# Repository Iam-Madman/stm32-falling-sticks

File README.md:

# stm32-falling-sticks

A DIY reaction-based "falling sticks" game controller built around an STM32 Bluepill.

## Features

- **STM32 Bluepill** as the main controller
- **10x electromagnet drivers (12v)** — MOSFET-switched, each with a flyback protection diode and pulldown resistor
- **10x Hall effect sensors (5v)** for stick drop/position detection
- **LCD output** support for game status/score
- **Buzzer (12v)** support, driven off the same MOSFET channels as the electromagnets
- **Start button** input to trigger the game
- **Single-layer PCB** — 0-ohm jumper resistors used in place of vias/second layer for a few connections
- **CNC-mill optimized** trace layout (tested on a Wegstr 3-axis CNC)

## Power

- Dual 12V input options: screw terminal or DC jack
- **MP1584EN buck converter** steps 12V down to 5V to power the electromagnets, Hall effect sensors, and Bluepill

## Board Previews

| View | Image |
| --- | --- |
| **Top View** |  |
| **Bottom View** |  |
| **Side View 1** |  |
| **Side View 2** |  |

## Schematics

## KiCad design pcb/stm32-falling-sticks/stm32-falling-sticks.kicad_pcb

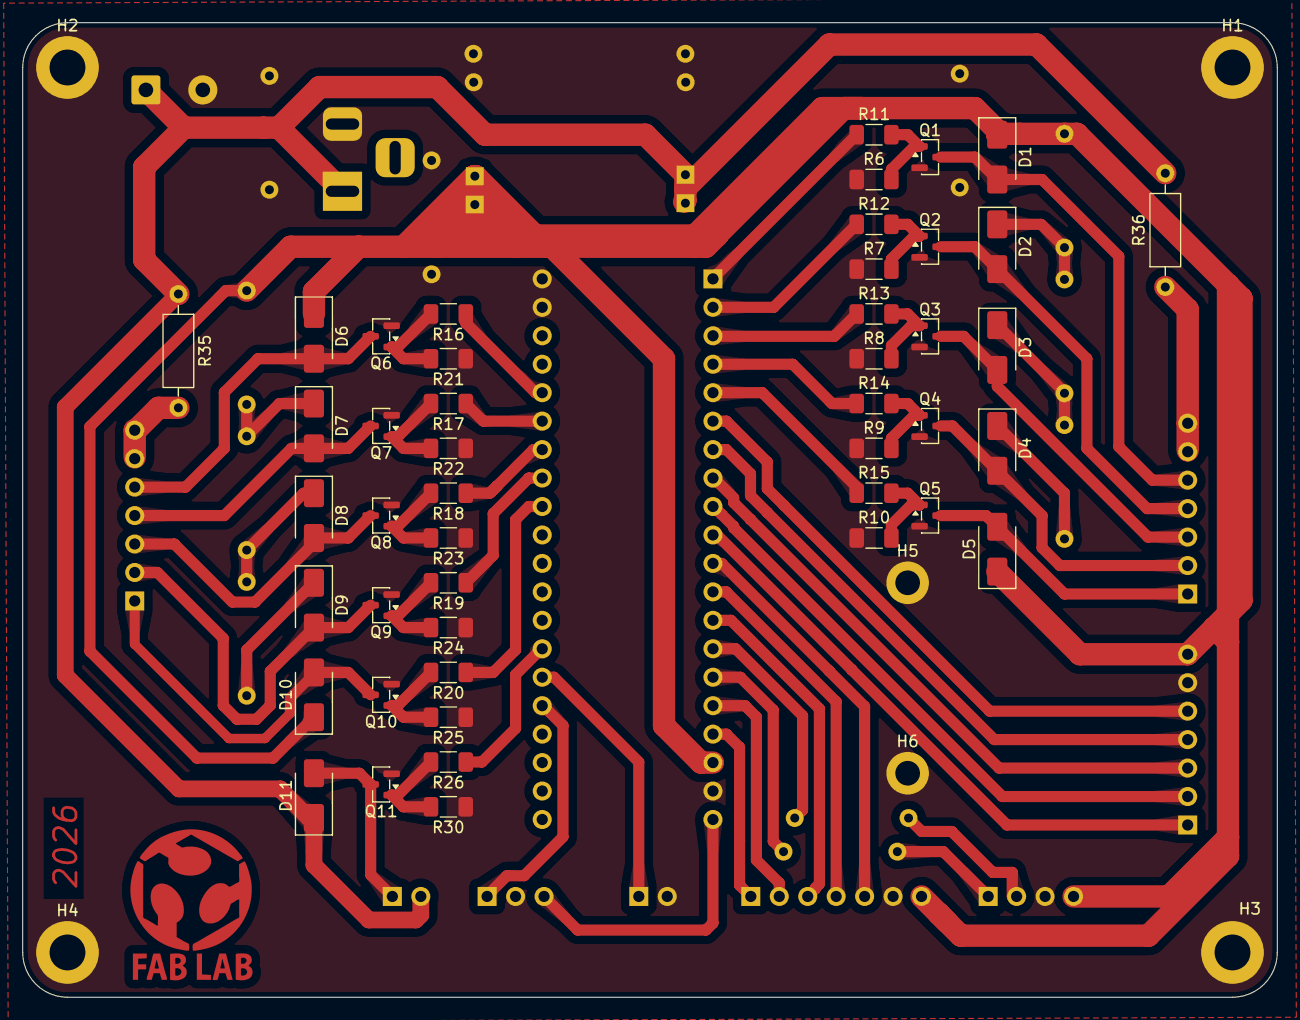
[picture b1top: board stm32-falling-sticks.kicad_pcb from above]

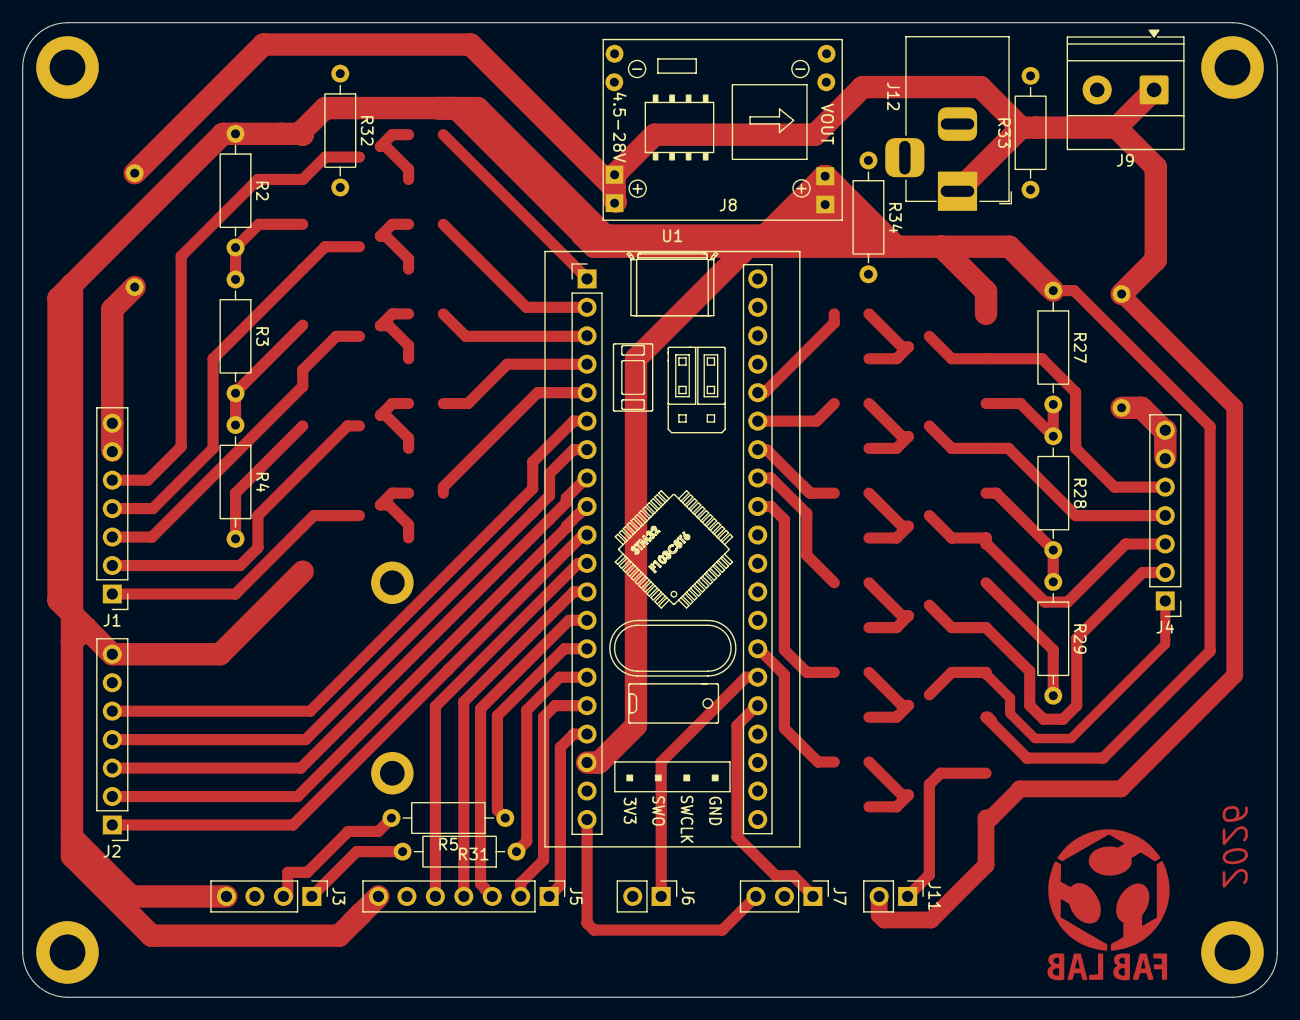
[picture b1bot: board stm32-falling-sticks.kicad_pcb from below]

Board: 2 copper layers, 112.0 x 87.0 mm, 75 parts (23 on the bottom side), 59 nets.

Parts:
D1, D2, D3, D4, D5, D6, D7, D8, D9, D10, D11: SS34; D_SMA
H1, H2, H3, H4: MountingHole_Pad; MountingHole_3.2mm_M3_DIN965_Pad
H5, H6: MountingHole_Pad; MountingHole_2.2mm_M2_DIN965_Pad
J1: MAG_01-05_OUT; PinHeader_1x07_P2.54mm_Vertical
J2: HAL_01-05_IN; PinHeader_1x07_P2.54mm_Vertical
J3: LCD_OUT; PinHeader_1x04_P2.54mm_Vertical
J4: MAG_06-10_OUT; PinHeader_1x07_P2.54mm_Vertical
J5: HAL_06-10_IN; PinHeader_1x07_P2.54mm_Vertical
J6: START_IN; PinHeader_1x02_P2.54mm_Vertical
J7: POT_IN; PinHeader_1x03_P2.54mm_Vertical
J8: MP1584EN; SRT_MPT1584EN_Module
J9: Screw_Terminal_01x02; TerminalBlock_Phoenix_MKDS-1,5-2-5.08_1x02_P5.08mm_Horizont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
J11: BUZ_OUT; PinHeader_1x02_P2.54mm_Vertical
J12: Barrel_Jack_MountingPin; BarrelJack_Horizontal
Q1, Q2, Q3, Q4, Q5, Q6, Q7, Q8, Q9, Q10, Q11: AO3400A; SOT-23
R2, R3, R4, R5, R27, R28, R29, R31, R32, R33, R34, R35, R36: 0; R_Axial_DIN0207_L6.3mm_D2.5mm_P10.16mm_Horizontal
R6, R7, R8, R9, R10, R21, R22, R23, R24, R25, R30: 10k; R_1206_3216Metric_Pad1.30x1.75mm_HandSolder
R11, R12, R13, R14, R15, R16, R17, R18, R19, R20, R26: 100; R_1206_3216Metric_Pad1.30x1.75mm_HandSolder
U1: YAAJ_BluePill_Part_Like_SWD_Breakout; YAAJ_BluePill_1

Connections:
+3V3: J7.3, U1.20 (3V3)
+5V: D1.1 (K), D5.1 (K), D6.1 (K), D10.1 (K), J2.7, J3.4, J5.7, J8.3, R2.1, R27.1, U1.18 (5V)
+12V: D11.1 (K), J1.6, J1.7, J4.6, J4.7, J8.1, J9.1, J11.2, J12.1, R35.1, R35.2, R36.1, R36.2
/BUZ_GND: D11.2 (A), J11.1, Q11.3 (D)
/HAL_01: J2.5, U1.6 (PA9)
/HAL_02: J2.4, U1.7 (PA10)
/HAL_03: J2.3, U1.8 (PA11)
/HAL_04: J2.2, U1.9 (PA12)
/HAL_05: J2.1, U1.10 (PA15)
/HAL_06: J5.5, U1.11 (PB3)
/HAL_07: J5.4, U1.12 (PB4)
/HAL_08: J5.3, U1.13 (PB5)
/HAL_09: J5.2, U1.16 (PB8)
/HAL_10: J5.1, U1.17 (PB9)
/LCD_SCL: R5.1, U1.14 (PB6)
/LCD_SDA: R31.1, U1.15 (PB7)
/MAG_01: D1.2 (A), J1.5, Q1.3 (D)
/MAG_02: D2.2 (A), J1.4, Q2.3 (D)
/MAG_03: D3.2 (A), J1.3, Q3.3 (D)
/MAG_04: D4.2 (A), J1.2, Q4.3 (D)
/MAG_05: D5.2 (A), J1.1, Q5.3 (D)
/MAG_06: D6.2 (A), J4.5, Q6.3 (D)
/MAG_07: D7.2 (A), J4.4, Q7.3 (D)
/MAG_08: D8.2 (A), J4.3, Q8.3 (D)
/MAG_09: D9.2 (A), J4.2, Q9.3 (D)
/MAG_10: D10.2 (A), J4.1, Q10.3 (D)
/POT_IN: J7.1, U1.25 (PA0)
/START_IN: J6.1, U1.26 (PA1)
GND: H1.1 (1_1), H2.1 (1_1), H3.1 (1_1), H4.1 (1_1), H5.1 (1_1), H6.1 (1_1), J2.6, J3.3, J5.6, J6.2, J7.2, J8.2, J8.4, J9.2, J12.2, Q1.2 (S), Q2.2 (S), Q3.2 (S), Q4.2 (S), Q5.2 (S), Q6.2 (S), Q7.2 (S), Q8.2 (S), Q9.2 (S), Q10.2 (S), Q11.2 (S), R6.1, R7.1, R8.1, R9.1, R10.1, R21.1, R22.1, R23.1, R24.1, R25.1, R30.1, R32.1, R32.2, R33.1, R33.2, R34.1, R34.2, U1.19 (GND), U1.39 (GND), U1.40 (GND)
unnamed: D2.1 (K), R2.2, R3.1
unnamed: D3.1 (K), R3.2, R4.1
unnamed: D4.1 (K), R4.2
unnamed: D7.1 (K), R27.2, R28.1
unnamed: D8.1 (K), R28.2, R29.1
unnamed: D9.1 (K), R29.2
unnamed: J3.1, R31.2
unnamed: J3.2, R5.2
unnamed: Q1.1 (G), R6.2, R11.2
unnamed: Q2.1 (G), R7.2, R12.2
unnamed: Q3.1 (G), R8.2, R13.2
unnamed: Q4.1 (G), R9.2, R14.2
unnamed: Q5.1 (G), R10.2, R15.2
unnamed: Q6.1 (G), R16.2, R21.2
unnamed: Q7.1 (G), R17.2, R22.2
unnamed: Q8.1 (G), R18.2, R23.2
unnamed: Q9.1 (G), R19.2, R24.2
unnamed: Q10.1 (G), R20.2, R25.2
unnamed: Q11.1 (G), R26.2, R30.2
unnamed: R26.1, U1.27 (PA2)
unnamed: R20.1, U1.32 (PA7)
unnamed: R15.1, U1.5 (PA8)
unnamed: R19.1, U1.33 (PB0)
unnamed: R18.1, U1.34 (PB1)
unnamed: R17.1, U1.35 (PB10)
unnamed: R16.1, U1.36 (PB11)
unnamed: R11.1, U1.1 (PB12)
unnamed: R12.1, U1.2 (PB13)
unnamed: R13.1, U1.3 (PB14)
unnamed: R14.1, U1.4 (PB15)
